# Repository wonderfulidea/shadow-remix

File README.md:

# Shadow Remix

Live demo at: [apps.wonderfulidea.co/shadow-remix/app/](https://apps.wonderfulidea.co/shadow-remix/app/)

- [Overview](#overview)
  - [Shadow Remix App](#shadow-remix-app)
  - [Online Gallery](#online-gallery)
  - [Gallery Admin Interface](#gallery-admin-interface)
  - [Arduino](#arduino)
  - [Repo Structure](#repo-structure)
- [Use](#use)
- [License](#license)
- [Hotkeys](#hotkeys)
- [Limitations](#limitations)
- [Parts List](#parts-list)
- [Schematics and PCB](#schematics-and-pcb)
- [Backend Setup](#backend-setup)
- [Serial Communication](#serial-communication)
- [Code](#code)
  - [Install nodejs and npm](#install-nodejs-and-npm)
  - [Compiling UI Library](#compiling-ui-library)
  - [Compiling Desktop App](#compiling-desktop-app)
  - [Adding Screensaver Animations](#adding-screensaver-animations)
  - [Compiling Gallery](#compiling-gallery)

## Overview

This project consists of a few pieces of code that interact with each other:

### Shadow Remix App

The Shadow Remix drawing interface is available both as javascript code that runs in a web browser *or* as a compiled desktop app for Windows and Mac.  A live demo of the code is hosted at [apps.wonderfulidea.co/shadow-remix/app/](https://apps.wonderfulidea.co/shadow-remix/app/).

The browser-based drawing interface does not have the ability to upload photos to [our online gallery](https://apps.wonderfulidea.co/shadow-remix/gallery/) due to security issues (we don't want to let anyone on the internet upload photos to the gallery), but it does let users save images to their computers.

You will need to [compile your own copy of the desktop Shadow Remix drawing interface](#compiling-desktop-app) with credentials for editing your database.

### Online Gallery

The gallery is a separate web app that displays approved photos drawn by visitors at the museum exhibition.  It has a feature where any new (unapproved) drawing made in the museum is shown for a brief period and then hidden until it is [approved by an admin](#gallery-admin-interface).

The gallery is currently hosted at [apps.wonderfulidea.co/shadow-remix/gallery/](https://apps.wonderfulidea.co/shadow-remix/gallery/).

### Gallery Admin Interface

The gallery admin interface is a private web app that displays saved photos drawn by visitors at the museum exhibition and allows an admin to approve them for public viewing.  You will need to [compile and host your own copy of the admin interface](#compiling-gallery) with credentials for editing your database.

### Arduino

The museum exhibit features a motorized shadow-making setup and a panel of button controls for easier interaction.  All the electronics for this exhibit are controlled by an [Arduino](https://www.arduino.cc/) which communicates via USB to the desktop app.

### Repo Structure

This repo consists of several subdirectories:

- [app](app) folder contains both a standalone browser-based application for shadow remix and the UI library code for connecting to a webcam, drawing to the screen, and saving images.
- [electron](electron) folder has code for compiling the desktop app with [Electron](https://www.electronjs.org/), it depends on the UI codebase located within the `app` folder.
- [gallery](gallery) folder has code for a publicly accessible gallery webpage showing images uploaded by users.
- [gallery-admin](gallery-admin) folder has code for a private admin interface for approving images.
- [arduino](arduino) folder contains arduino code for connecting hardware buttons to the app.

## Use

You need to compile your own Windows (64 and 32 bit) and Mac installers following the instructions for [compiling the desktop app](#compiling-desktop-app).  Once built, you should be able to install the app on any desktop setup.  These app is not signed and may require some additional steps to open:

- On Mac, hold down the control key and right click on the application icon, then select `Open`.  Confirm that you would like to open the application by an unidentified developer.  You should only need to do this the first time you run the application.  More info [here](https://support.apple.com/guide/mac-help/open-a-mac-app-from-an-unidentified-developer-mh40616/mac).

The first time you open the app, it will ask permission to access the webcam in a pop-up dialog.

## License

This work is distributed under an MIT license with exception to the "Lunch" font by Anthem Type.  See [Lunch Font](https://www.fontspace.com/lunch-font-f3679) for more details about licensing.

## Hotkeys

This app is primarily intended for use in a museum environment via a touchscreen and peripheral button controls.  If you have access to a keyboard or MakeyMakey, you can also use the following hotkeys:

- `ctrl/command` + `z` OR `d` to undo
- `ctrl/command` + `s` OR `a` to save image
- `backspace/delete` OR `g` to clear
- `c` brings up a dialog for selecting the webcam device
- `p` brings up a dialog for selecting the serial port (desktop app only)
- `v` saves your current drawing as an animated video (webm format).  Webm videos are large and difficult to play, but very fast to save – which is why we use them.  You can also use video editing software like Adobe Premiere to convert the video format.  Once you have the mp4s, you can [add them to the desktop app](#adding-screensaver-animations).
- `h` puts the app into screen saver mode (desktop app only).

## Limitations

- Currently, this app expects to receive webcam feeds in landscape orientation and renders out at the resolution specified in [app/src/constants.ts](app/src/constants.ts).  I've noticed that when mobile devices are in portrait mode, the returned width and height from `getUserMedia()` look like the stream is still in landscape.  I have not found a consistent way to correct this yet.

## Parts List

See [docs/Parts_List.md](docs/Parts_List.md) for a list of hardware we used for our exhibit.

## Schematics and PCB

See [docs/PCB.md](docs/PCB.md) for schematics and info about making circuit boards for the exhibit.

## Backend Setup

This app uses an AWS S3 bucket to store saved images in the cloud.  The saved images can be viewed through a webpage at [apps.wonderfulidea.co/shadow-remix/gallery/](https://apps.wonderfulidea.co/shadow-remix/gallery/).  Info about configuring the AWS Backend can be found at [docs/Backend_Setup.md](docs/Backend_Setup.md).

## Serial Communication

The serial communication protocol between the desktop app and Arduino is described in [docs/Serial_Communication.md](docs/Serial_Communication.md).  All arduino code can be found in the [arduino](arduino) folder.

## Code

### Install nodejs and npm

Before you compile any part of the code, you will need to [install nodejs and npm](https://docs.npmjs.com/downloading-and-installing-node-js-and-npm) on your machine.  All compilation steps are done through the command line.

### Compiling UI Library

This repo comes with a pre-built version of the UI library, located at [app/dist/ui.js](app/dist/ui.js).  This library should be fine as is for most cases.  **If you do not plan to modify the UI code, skip to the [next section](#compiling-desktop-app).**

If you want to change the available colors, line thicknesses, and other aspects of the UI, you can make those edits within
[app/src/constants.ts](app/src/constants.ts).

If you want to change the hotkeys, you can make those edits within
[app/src/hotkeys.ts](app/src/hotkeys.ts).

After make changes to the UI code you need to compile the `app/src/` folder to `app/dist/` using the following commands:

First, [install nodejs and npm](#install-nodejs-and-npm).

In the terminal, navigate to the `app` directory:
```sh
cd app
```

Install all dependencies:
```sh
npm install
```

Compile with [Webpack](https://webpack.js.org/):
```sh
npm run build
```

You can also start a development server at [localhost:8080/](http://localhost:8080/) using the following command:
```sh
npm run start
```

### Compiling Desktop App

The javascript code in this repo is compiled with [Electron](https://www.electronjs.org/) so that it can be run as a desktop app (rather than in a web browser).

You will need to compile your own desktop app after following the steps to [set up an AWS bucket and permissions](docs/Backend_Setup.md) and create an `.env` file with your access keys.  If make changes to the UI library in the `app` directory, you will need to [compile it first](#compiling-ui-library) before compiling a new copy of the desktop app.

If you want to change things about the app's functionality (e.g. wait time before showing the screensaver, or which buttons map to which functions) you can make those edits within
[electron/src/constants.ts](electron/src/constants.ts).

To compile for Windows and Mac:

First, [install nodejs and npm](#install-nodejs-and-npm).

In the terminal, navigate to the `electron` directory:
```sh
cd electron
```

Install all dependencies:
```sh
npm install
```

To compile for Windows and Mac:
```sh
npm run build
```

Once complete, builds are located in the `electron/build` folder.  The `shadow-remix Setup #.#.#.exe` installer should work on 32bit and 64 bit Windows machines, and the `shadow-remix-#.#.#.dmg` or `shadow-remix-#.#.#-mac.zip` files contain builds for Mac.

If you would like to compile for Linux, edit the following line in [electron/package.json](electron/package.json):

```json
"build": "npm run compile && electron-builder -mw",
```

change to:

```json
"build": "npm run compile && electron-builder -mwl",
```

Then run:

```sh
npm run build
```

Linux build has not been tested and may require additional configs, see the [electron-builder docs](https://www.electron.build/multi-platform-build.html) for more information.

If you want to make changes to the app's code, you can quickly test them by running a local development server:
```sh
npm run start
```
This will open an app window and begin running the new code automatically.

### Adding Screensaver Animations

The desktop app features a screensaver mode where you can show animations of previously drawn shadow-remixes if the station has remained inactive for a period of time.  To create the videos, draw a shadow remix and then hit the `v` key when you are done.  This will step through your entire drawing sequence and save out a video (it may be a little slow).  Using a video editor, convert the webm videos that are saved to your computer into mp4.

Next, you need to create a folder at `electron/animations/` and add several videos to this folder (with format mp4).  After making these changes you will need to recompile the app.  Alternatively, if you would like to change these videos (or add new ones) without recompiling the app, you can edit the contents of the `Resources/animations/` folder in the app's build and restart the app (on Mac, right click on the app's icon and select "Show Package Contents", on Windows right click on the app's icon and select "More > Open file location").  To be safe, use filenames without spaces for any animations you add to the app.

### Compiling Gallery

This repo comes with a pre-built version of our public gallery, located at [gallery/dist/](gallery/dist/) and currently hosted at XXXX.

In order to view your own images, you will need to recompile the gallery after [setting up your AWS bucket and permissions](docs/Backend_Setup.md) and creating a `.env` file with your access keys.

You can also edit some parameters of the gallery (e.g. how long images stay up, how often to refresh) at the top of [gallery/src/index.ts](gallery/src/index.ts).

Once complete, compile the `gallery/src/` folder to `gallery/dist/` using the following commands:

First, [install nodejs and npm](#install-nodejs-and-npm).

In the terminal, navigate to the `gallery` directory:
```sh
cd gallery
```

Install all dependencies:
```sh
npm install
```

Compile with [Webpack](https://webpack.js.org/):
```sh
npm run build
```

You can also start a development server at [localhost:8080/](http://localhost:8080/) using the following command:
```sh
npm run start
```

Note that you will also need to add `http://localhost:8080` to you list of Allowed Origins in the [AWS backend setup](https://github.com/amandaghassaei/shadow-remix/blob/main/docs/Backend_Setup.md#enable-cross-origin-requests).

Follow these same instructions to compile the gallery admin interface (located in the [gallery-admin](gallery-admin) folder).  Once compiled, the files inside [gallery-admin/dist/](gallery-admin/dist/) can be run locally or [hosted behind a password protected server](docs/Backend_Setup.md#hosting-private-admin-server) to allow admins to approve new image that are saved from the app.  **Do not post the compiled gallery-admin interface publicly because it contains your AWS secrete keys!!**  By default, all files in `gallery-admin/dist` (with the exception of index.html) should be ignored from git.

You can edit some parameters of the gallery admin interface (e.g. how often to refresh) at the top of [gallery-admin/src/index.ts](gallery-admin/src/index.ts).

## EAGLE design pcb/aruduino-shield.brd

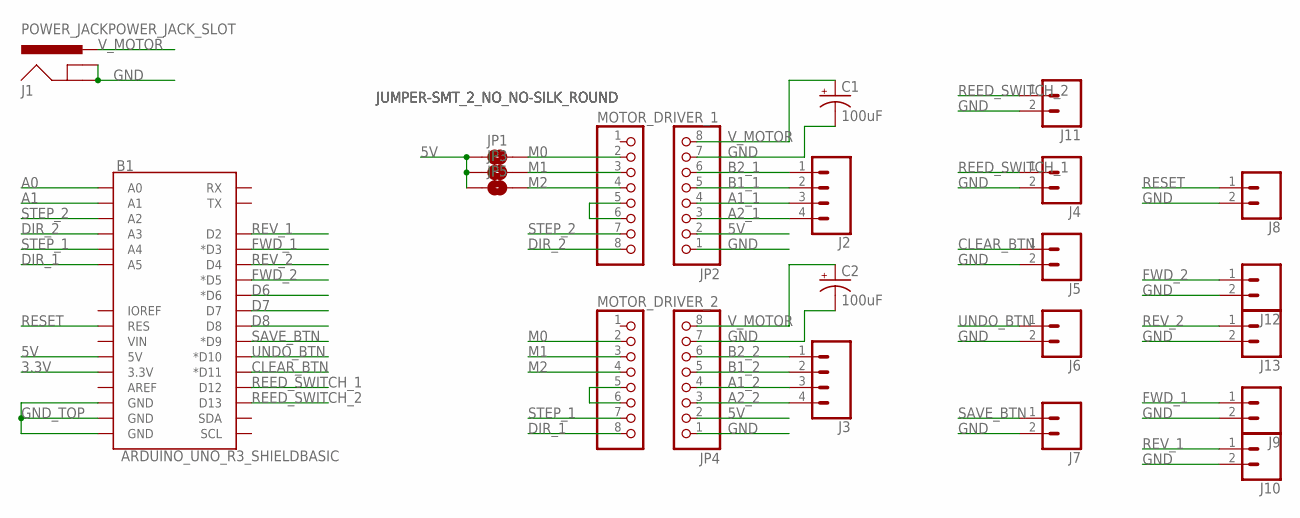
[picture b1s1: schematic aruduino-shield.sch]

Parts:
B1: ARDUINO_UNO_R3_SHIELDBASIC; UNO_R3_SHIELD
C1, C2: 100uF; CPOL-RADIAL-2.5MM-6.5MM
J1: POWER_JACKPOWER_JACK_SLOT; POWER_JACK_PTH_SLOT
J2, J3: CONN_04SCREW; SCREWTERMINAL-3.5MM-4
J4, J5, J6, J7, J8, J9, J10, J11, J12, J13: CONN_02; 1X02
JP1, JP3, JP5: JUMPER-SMT_2_NO_NO-SILK_ROUND; SMT-JUMPER_2_NO_NO-SILK_ROUND
JP2, JP4: PINHD-1X8CLEANBIG; 1X08-CLEANBIG
MOTOR_DRIVER_1, MOTOR_DRIVER_2: PINHD-1X8CLEANBIG; 1X08-CLEANBIG

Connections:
3.3V: B1.3.3V
5V: B1.5V, JP1.1, JP2.2, JP3.1, JP4.2, JP5.1
A0: B1.A0
A1: B1.A1
A1_1: J2.3, JP2.4
A1_2: J3.3, JP4.4
A2_1: J2.4, JP2.3
A2_2: J3.4, JP4.3
B1_1: J2.2, JP2.5
B1_2: J3.2, JP4.5
B2_1: J2.1, JP2.6
B2_2: J3.1, JP4.6
CLEAR_BTN: B1.D11 (*D11), J5.1
D6: B1.D6 (*D6)
D7: B1.D7
D8: B1.D8
DIR_1: B1.A5, MOTOR_DRIVER_2.8
DIR_2: B1.A3, MOTOR_DRIVER_1.8
FWD_1: B1.D3 (*D3), J9.1
FWD_2: B1.D5 (*D5), J12.1
GND: C1.2 (-), C2.2 (-), J1.GND, J1.GNDBREAK, J4.2, J5.2, J6.2, J7.2, J8.2, J9.2, J10.2, J11.2, J12.2, J13.2, JP2.1, JP2.7, JP4.1, JP4.7
GND_TOP: B1.GND@0 (GND), B1.GND@1 (GND), B1.GND@2 (GND)
M0: JP1.2, MOTOR_DRIVER_1.2, MOTOR_DRIVER_2.2
M1: JP3.2, MOTOR_DRIVER_1.3, MOTOR_DRIVER_2.3
M2: JP5.2, MOTOR_DRIVER_1.4, MOTOR_DRIVER_2.4
unnamed: MOTOR_DRIVER_2.5, MOTOR_DRIVER_2.6
unnamed: MOTOR_DRIVER_1.5, MOTOR_DRIVER_1.6
REED_SWITCH_1: B1.D12, J4.1
REED_SWITCH_2: B1.D13, J11.1
RESET: B1.RES, J8.1
REV_1: B1.D2, J10.1
REV_2: B1.D4, J13.1
SAVE_BTN: B1.D9 (*D9), J7.1
STEP_1: B1.A4, MOTOR_DRIVER_2.7
STEP_2: B1.A2, MOTOR_DRIVER_1.7
UNDO_BTN: B1.D10 (*D10), J6.1
V_MOTOR: C1.1 (+), C2.1 (+), J1.PWR, JP2.8, JP4.8

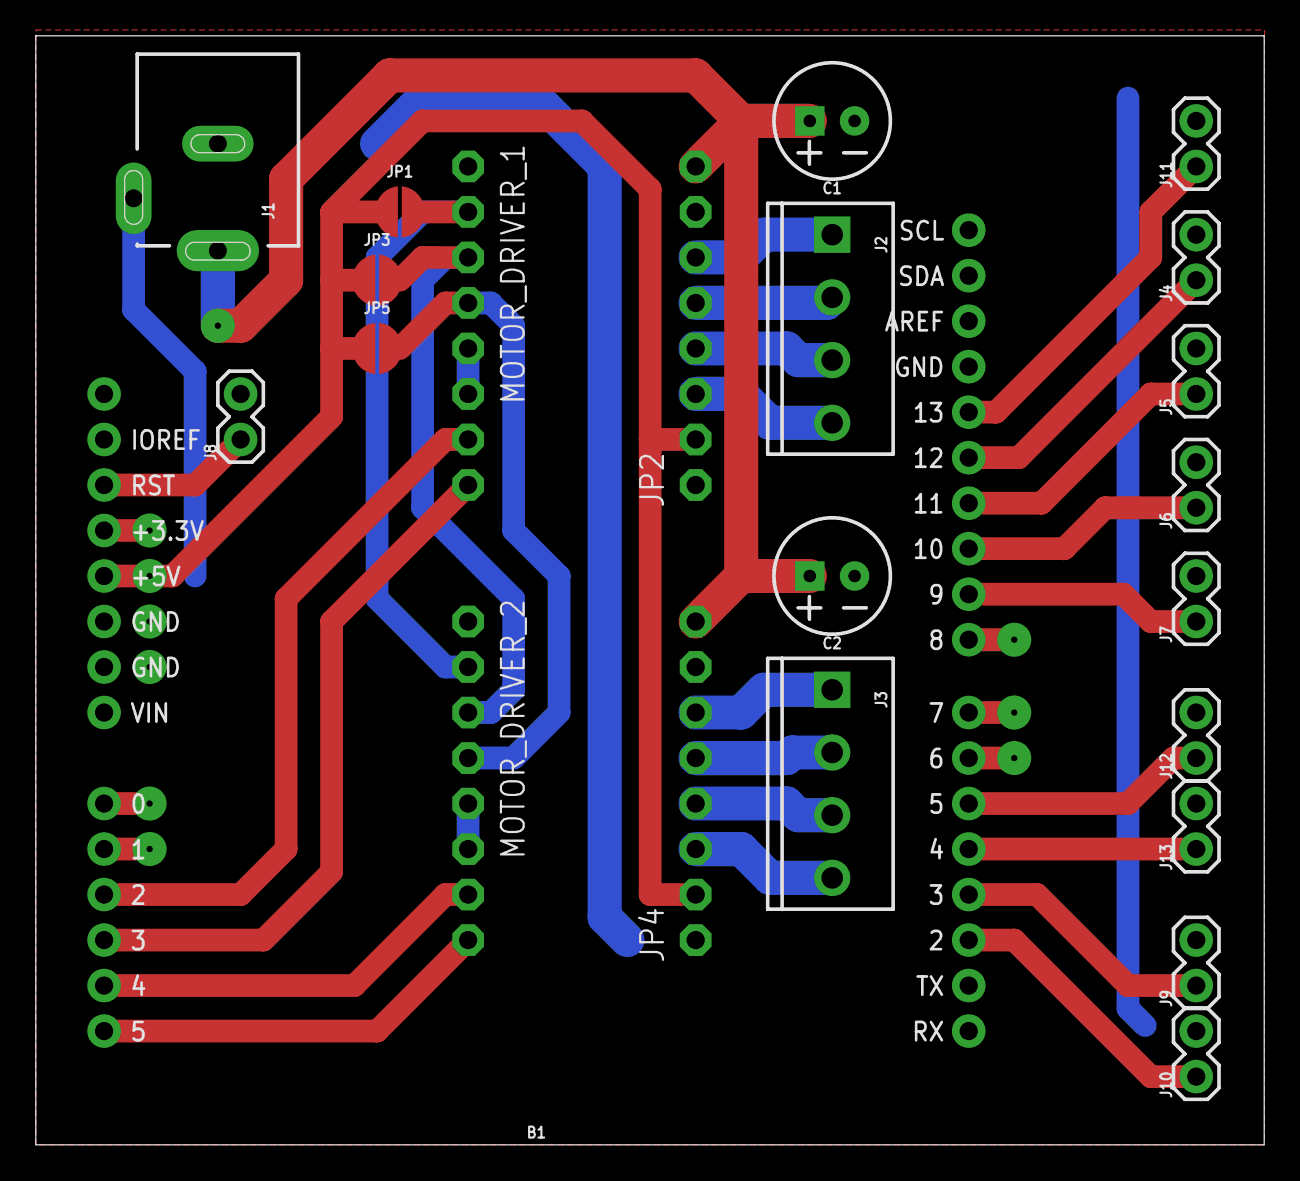
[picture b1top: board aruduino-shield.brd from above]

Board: 2 copper layers, 68.6 x 61.9 mm, 23 parts (0 on the bottom side), 31 nets.

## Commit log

2022-07-13 license
2022-07-14 readme, moving things around
2022-07-14 readme
2022-07-14 moving app index
2022-07-14 moving gallery index to root
2022-07-14 moving gallery admin index to root
2022-07-15 docs, small changes
2022-07-15 comments
2022-07-23 small fixes
2022-07-24 fix ui glitch
2022-07-24 small changes
2022-07-24 station id fixes
2022-07-25 better zeroing routine
2022-07-26 parts list
2022-07-26 wiring diagram
2022-07-26 hotkey changes, readme
2022-08-13 limits on aws calls

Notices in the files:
parts and their libraries:
SparkFun-Boards: Licensing: Creative Commons ShareAlike 4.0 International - https://creativecommons.org/licenses/by-sa/4.0
